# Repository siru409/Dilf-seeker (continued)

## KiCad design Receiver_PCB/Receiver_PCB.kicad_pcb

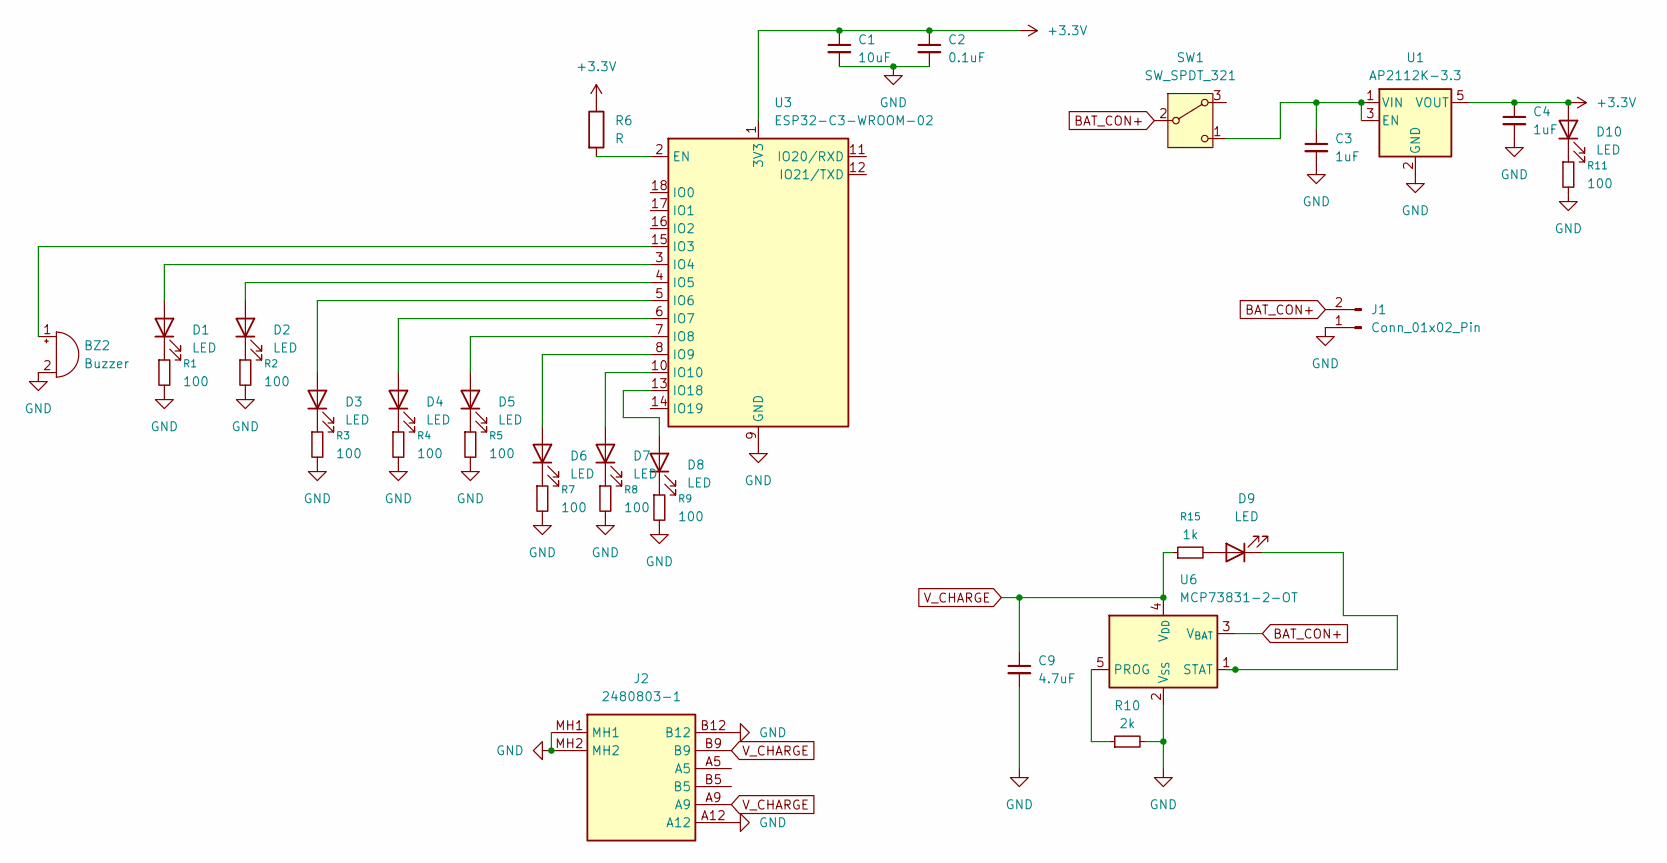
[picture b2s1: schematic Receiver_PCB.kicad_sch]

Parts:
BZ2: Buzzer; Buzzer_TDK_PS1240P02BT_D12.2mm_H6.5mm
C1: 10uF; C_0603_1608Metric
C2: 0.1uF; C_0603_1608Metric
C3, C4: 1uF; C_0603_1608Metric
C9: 4.7uF; C_0603_1608Metric
D1, D2, D3, D4, D5, D6, D7, D8, D10: LED; D_0603_1608Metric_Pad1.05x0.95mm_HandSolder
D9: LED; LED_0603_1608Metric_Pad1.05x0.95mm_HandSolder
J1: Conn_01x02_Pin; PinHeader_1x02_P2.54mm_Vertical
J2: 2480803-1; 24808031; Mouser Part Number 571-2480803-1
R1, R2, R3, R4, R5, R7, R8, R9, R11: 100; R_0603_1608Metric
R6: R; R_0603_1608Metric
R10: 2k; R_0603_1608Metric
R15: 1k; R_0603_1608Metric
SW1: SW_SPDT_321; SW_XKB_DM1-16UP-1
U1: AP2112K-3.3; SOT-23-5
U3: ESP32-C3-WROOM-02
U6: MCP73831-2-OT; SOT-23-5

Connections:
+3.3V: C1.1, C2.1, C4.1, D10.2 (A), R6.1, U1.5 (VOUT), U3.1 (3V3)
BAT_CON+: J1.2, SW1.2 (B), U6.3 (V_{BAT})
GND: BZ2.2 (-), C1.2, C2.2, C3.2, C4.2, C9.2, J1.1, J2.A12, J2.B12, J2.MH1, J2.MH2, R1.2, R2.2, R3.2, R4.2, R5.2, R7.2, R8.2, R9.2, R10.2, R11.2, U1.2 (GND), U3.9 (GND), U3.19 (GND), U6.2 (V_{SS})
unnamed: BZ2.1 (+), U3.15 (IO3)
unnamed: D1.2 (A), U3.3 (IO4)
unnamed: D1.1 (K), R1.1
unnamed: D2.2 (A), U3.4 (IO5)
unnamed: D2.1 (K), R2.1
unnamed: D3.2 (A), U3.5 (IO6)
unnamed: D3.1 (K), R3.1
unnamed: D4.2 (A), U3.6 (IO7)
unnamed: D4.1 (K), R4.1
unnamed: D5.2 (A), U3.7 (IO8)
unnamed: D5.1 (K), R5.1
unnamed: D6.2 (A), U3.8 (IO9)
unnamed: D6.1 (K), R7.1
unnamed: D7.2 (A), U3.10 (IO10)
unnamed: D7.1 (K), R8.1
unnamed: D8.2 (A), U3.13 (IO18)
unnamed: D8.1 (K), R9.1
unnamed: D9.2 (A), R15.2
unnamed: D9.1 (K), U6.1 (STAT)
unnamed: D10.1 (K), R11.1
unnamed: C3.1, SW1.1 (C), U1.1 (VIN), U1.3 (EN)
unnamed: R6.2, U3.2 (EN)
unnamed: R10.1, U6.5 (PROG)
V_CHARGE: C9.1, J2.A9, J2.B9, R15.1, U6.4 (V_{DD})

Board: 2 copper layers, 34 parts (1 on the bottom side), 27 nets, no tracks yet.

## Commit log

2025-10-25 work...
2025-10-25 adding symbols
2025-10-26 RX chain improvements and negative supply
2025-10-26 Structure +2.nd rx channel
2025-10-28 better adc, easyer rx chain design
2025-10-30 new mcu , swd interface
2025-10-30 mcu interfaces
2025-10-30 finishing up schematic
2025-10-30 efficiency boost
2025-10-30 battery system angefangen
2025-12-13 layout
2025-12-28 sruff
